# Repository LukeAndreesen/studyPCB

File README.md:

This project is a study timer that is meant to enforce productivity; an onboard
IR sensor, as well as a daughter-board hall-effect sensor module detect
a user's presence and ensure their phone is sitting on the desk and not in 
their hands. 3 daisy-chaineed shift registers control the 7-segment displays, 
and a magnetic buzzer and onboard LED's provide feedback and alerts. The 
devce connects to the user's computer via USB for power and serial connectivity
with the UI which can be interacted with using the board's buttons and 
potentiometer dial. This was my first independent PCB board, and I really
enjoyed the process of designing, soldering, and programming it!

A Bill of Materials is available as CSV in this repo, along with KiCad schematics.

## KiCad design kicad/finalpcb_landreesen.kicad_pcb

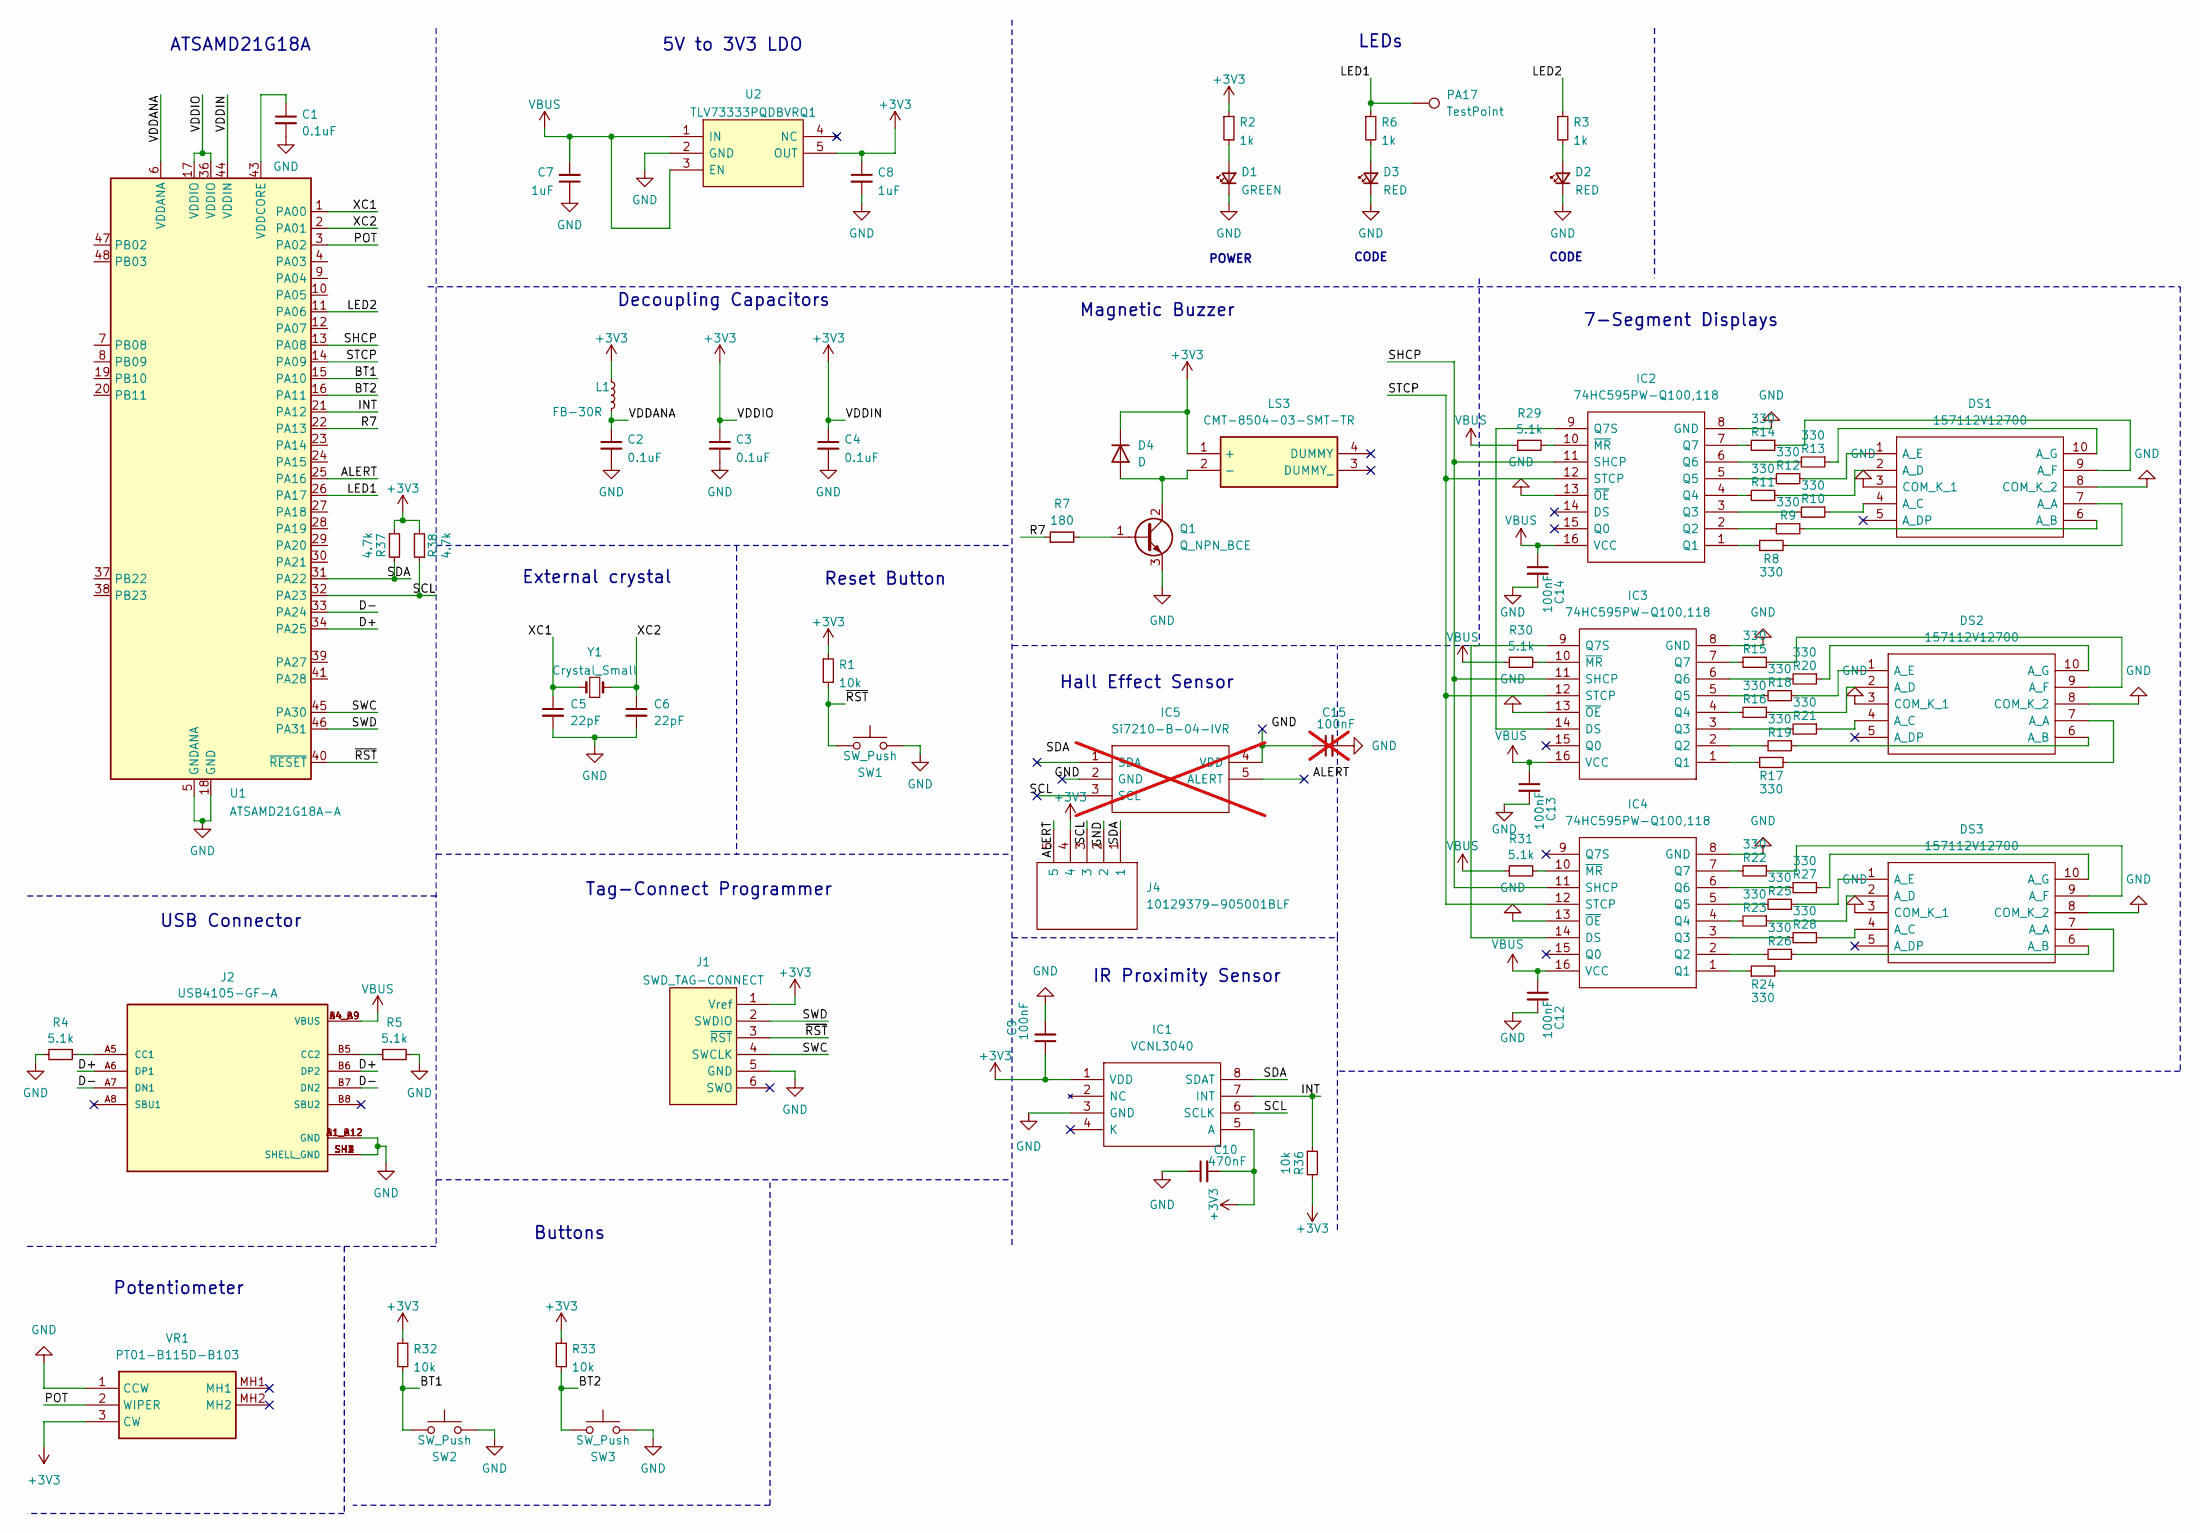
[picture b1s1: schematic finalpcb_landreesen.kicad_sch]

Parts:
C1, C2, C3, C4: 0.1uF; C_0603_1608Metric_Pad1.08x0.95mm_HandSolder
C5, C6: 22pF; C_0603_1608Metric_Pad1.08x0.95mm_HandSolder; Mouser Part Number 581-06035C220JAT2A
C7, C8: 1uF; C_0603_1608Metric_Pad1.08x0.95mm_HandSolder
C9, C12, C13, C14: 100nF; C_0603_1608Metric_Pad1.08x0.95mm_HandSolder
C10: 470nF; C_0603_1608Metric_Pad1.08x0.95mm_HandSolder
C15: 100nF; C_0603_1608Metric_Pad1.08x0.95mm_HandSolder; not fitted
D1: GREEN; LED_0603_1608Metric_Pad1.05x0.95mm_HandSolder
D2, D3: RED; LED_0603_1608Metric_Pad1.05x0.95mm_HandSolder; Mouser Part Number 710-150060RS55040
D4: D; SOD2713X115N
DS1, DS2, DS3: 157112V12700; Mouser Part Number 710-157112V12700
IC1: VCNL3040; SON108P200X400X115-8N; Mouser Part Number 78-VCNL3040
IC2, IC3, IC4: 74HC595PW-Q100,118; SOP65P640X110-16N; Mouser Part Number 771-74HC595PW-Q100
IC5: Si7210-B-04-IVR; SOT95P275X125-5N; Mouser Part Number 634-SI7210-B-04-IVR; not fitted
J1: SWD_TAG-CONNECT; Tag-Connect_TC2030-IDC-FP_2x03_P1.27mm_Vertical
J2: USB4105-GF-A; GCT_USB4105-GF-A
J4: 10129379-905001BLF; HDRRA5W67P0X254_1X5_1270X254X241P; Manufacturer_Part_Number 10129379-905001BLF
L1: FB-30R; L_0603_1608Metric_Pad1.05x0.95mm_HandSolder
LS3: CMT-8504-03-SMT-TR; CMT850403SMTTR; Mouser Part Number 179-CMT-8504-03SMTTR
PA17: TestPoint; TestPoint_Pad_D1.5mm
Q1: Q_NPN_BCE; 2SA1588GRLF
R1, R32, R33, R36: 10k; R_0603_1608Metric_Pad0.98x0.95mm_HandSolder
R2, R3, R6: 1k; R_0603_1608Metric_Pad0.98x0.95mm_HandSolder
R4, R5, R29, R30, R31: 5.1k; R_0603_1608Metric_Pad0.98x0.95mm_HandSolder
R7: 180; R_0603_1608Metric_Pad0.98x0.95mm_HandSolder
R8, R9, R10, R11, R12, R13, R14, R15, R16, R17, R18, R19, R20, R21, R22, R23, R24, R25, R26, R27, R28: 330; R_0603_1608Metric_Pad0.98x0.95mm_HandSolder
R37, R38: 4.7k; R_0603_1608Metric_Pad0.98x0.95mm_HandSolder
SW1, SW2, SW3: SW_Push; SW_SPST_TL3305A
U1: ATSAMD21G18A-A; TQFP-48_7x7mm_P0.5mm
U2: TLV73333PQDBVRQ1; SOT95P280X145-5N; Mouser Part Number 595-TLV73333PQDBVRQ1
VR1: PT01-B115D-B103; PT01B115DB103; Mouser Part Number 179-PT01-B115D-B103
Y1: Crystal_Small; Crystal_SMD_3215-2Pin_3.2x1.5mm; Mouser Part Number 815-ABS07-32.768KHZT

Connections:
+3V3: C3.1, C4.1, C8.1, C9.1, C10.2, D4.1 (K), IC1.1 (VDD), IC1.5 (A), J1.1 (Vref), J4.4, L1.1, LS3.1 (+), R1.1, R2.1, R32.1, R33.1, R36.2, R37.1, R38.2, U1.17 (VDDIO), U1.36 (VDDIO), U1.44 (VDDIN), U2.5 (OUT), VR1.3 (CW)
/ALERT: J4.5, U1.25 (PA16)
/BT1: R32.2, SW2.1, U1.15 (PA10)
/BT2: R33.2, SW3.1, U1.16 (PA11)
/D+: J2.A6 (DP1), J2.B6 (DP2), U1.34 (PA25)
/D-: J2.A7 (DN1), J2.B7 (DN2), U1.33 (PA24)
/INT: IC1.7 (INT), R36.1, U1.21 (PA12)
/LED1: PA17.1, R6.1, U1.26 (PA17)
/LED2: R3.1, U1.11 (PA06)
/POT: U1.3 (PA02), VR1.2 (WIPER)
/R7: R7.1, U1.22 (PA13)
/SCL: IC1.6 (SCLK), J4.3, R38.1, U1.32 (PA23)
/SDA: IC1.8 (SDAT), J4.1, R37.2, U1.31 (PA22)
/SHCP: IC2.11 (SHCP), IC3.11 (SHCP), IC4.11 (SHCP), U1.13 (PA08)
/STCP: IC2.12 (STCP), IC3.12 (STCP), IC4.12 (STCP), U1.14 (PA09)
/SWC: J1.4 (SWCLK), U1.45 (PA30)
/SWD: J1.2 (SWDIO), U1.46 (PA31)
/VDDANA: C2.1, L1.2, U1.6 (VDDANA)
/XC1: C5.1, U1.1 (PA00), Y1.2
/XC2: C6.1, U1.2 (PA01), Y1.1
/~RST: J1.3 (~RST), R1.2, SW1.1, U1.40 (~RESET)
GND: C1.2, C2.2, C3.2, C4.2, C5.2, C6.2, C7.1, C8.2, C9.2, C10.1, C12.2, C13.2, C14.2, C15.2, D1.1 (K), D2.1 (K), D3.1 (K), DS1.3 (COM_K_1), DS1.8 (COM_K_2), DS2.3 (COM_K_1), DS2.8 (COM_K_2), DS3.3 (COM_K_1), DS3.8 (COM_K_2), IC1.3 (GND), IC2.8 (GND), IC2.13 (~OE), IC3.8 (GND), IC3.13 (~OE), IC4.8 (GND), IC4.13 (~OE), J1.5 (GND), J2.A1_B12 (GND), J2.B1_A12 (GND), J2.SH1 (SHELL_GND), J2.SH2 (SHELL_GND), J2.SH3 (SHELL_GND), J2.SH4 (SHELL_GND), J4.2, Q1.3 (E), R4.2, R5.2, SW1.2, SW2.2, SW3.2, U1.5 (GNDANA), U1.18 (GND), U1.35 (GND), U1.42 (GND), U2.2 (GND), VR1.1 (CCW)
unnamed: C15.1, IC5.4 (VDD)
unnamed: D1.2 (A), R2.2
unnamed: D2.2 (A), R3.2
unnamed: D3.2 (A), R6.2
unnamed: D4.2 (A), LS3.2 (-), Q1.2 (C)
unnamed: DS1.7 (A_A), R8.2
unnamed: DS1.6 (A_B), R9.1
unnamed: DS1.4 (A_C), R10.1
unnamed: DS1.2 (A_D), R11.1
unnamed: DS1.1 (A_E), R12.1
unnamed: DS1.9 (A_F), R14.1
unnamed: DS1.10 (A_G), R13.1
unnamed: DS2.7 (A_A), R17.2
unnamed: DS2.6 (A_B), R19.1
unnamed: DS2.4 (A_C), R21.1
unnamed: DS2.2 (A_D), R16.1
unnamed: DS2.1 (A_E), R18.1
unnamed: DS2.9 (A_F), R15.1
unnamed: DS2.10 (A_G), R20.1
unnamed: DS3.7 (A_A), R24.2
unnamed: DS3.6 (A_B), R26.1
unnamed: DS3.4 (A_C), R28.1
unnamed: DS3.2 (A_D), R23.1
unnamed: DS3.1 (A_E), R25.1
unnamed: DS3.9 (A_F), R22.1
unnamed: DS3.10 (A_G), R27.1
unnamed: IC2.1 (Q1), R8.1
unnamed: IC2.2 (Q2), R9.2
unnamed: IC2.3 (Q3), R10.2
unnamed: IC2.4 (Q4), R11.2
unnamed: IC2.5 (Q5), R12.2
unnamed: IC2.6 (Q6), R13.2
unnamed: IC2.7 (Q7), R14.2
unnamed: IC2.9 (Q7S), IC3.14 (DS)
unnamed: IC2.10 (~MR), R29.2
unnamed: IC3.1 (Q1), R17.1
unnamed: IC3.2 (Q2), R19.2
unnamed: IC3.3 (Q3), R21.2
unnamed: IC3.4 (Q4), R16.2
unnamed: IC3.5 (Q5), R18.2
unnamed: IC3.6 (Q6), R20.2
unnamed: IC3.7 (Q7), R15.2
unnamed: IC3.9 (Q7S), IC4.14 (DS)
unnamed: IC3.10 (~MR), R30.2
unnamed: IC4.1 (Q1), R24.1
unnamed: IC4.2 (Q2), R26.2
unnamed: IC4.3 (Q3), R28.2
unnamed: IC4.4 (Q4), R23.2
unnamed: IC4.5 (Q5), R25.2
unnamed: IC4.6 (Q6), R27.2
unnamed: IC4.7 (Q7), R22.2
unnamed: IC4.10 (~MR), R31.2
unnamed: J2.A5 (CC1), R4.1
unnamed: J2.B5 (CC2), R5.1
unnamed: Q1.1 (B), R7.2
unnamed: C1.1, U1.43 (VDDCORE)
VBUS: C7.2, C12.1, C13.1, C14.1, IC2.16 (VCC), IC3.16 (VCC), IC4.16 (VCC), J2.A4_B9 (VBUS), J2.B4_A9 (VBUS), R29.1, R30.1, R31.1, U2.1 (IN), U2.3 (EN)

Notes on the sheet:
Buttons
5V to 3V3 LDO
External crystal
Tag-Connect Programmer
Decoupling Capacitors
Magnetic Buzzer
CODE
7-Segment Displays
LEDs
IR Proximity Sensor
POWER
Hall Effect Sensor
USB Connector
Potentiometer
ATSAMD21G18A
Reset Button

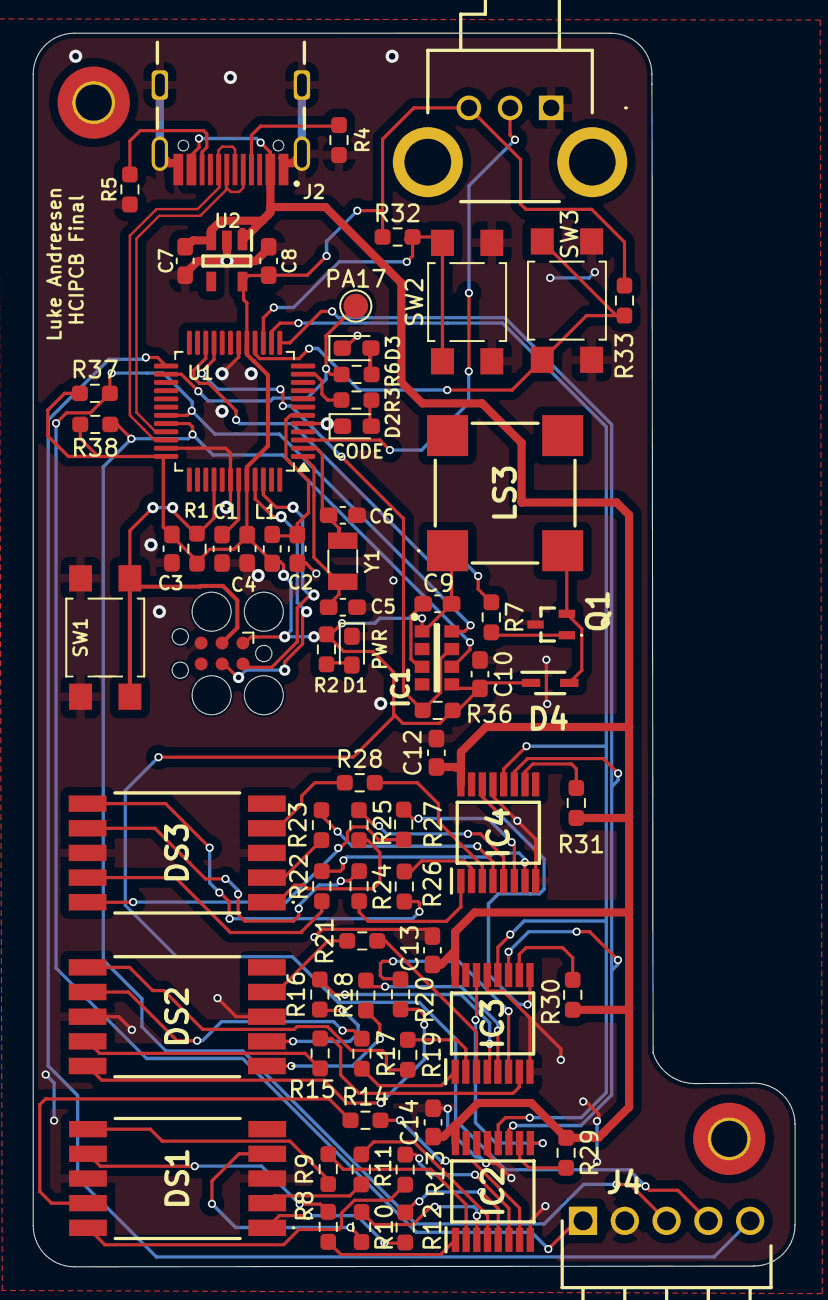
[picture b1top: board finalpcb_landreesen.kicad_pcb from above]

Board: 2 copper layers, 46.3 x 75.0 mm, 74 parts (0 on the bottom side), 78 nets.

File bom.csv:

"Reference","Value","Datasheet","Footprint","Qty","DNP"
"C1,C2,C3,C4","0.1uF","~","Capacitor_SMD:C_0603_1608Metric_Pad1.08x0.95mm_HandSolder","4",""
"C5,C6","22pF","~","Capacitor_SMD:C_0603_1608Metric_Pad1.08x0.95mm_HandSolder","2",""
"C7,C8","1uF","~","Capacitor_SMD:C_0603_1608Metric_Pad1.08x0.95mm_HandSolder","2",""
"C9,C12,C13,C14","100nF","~","Capacitor_SMD:C_0603_1608Metric_Pad1.08x0.95mm_HandSolder","4",""
"C10","470nF","~","Capacitor_SMD:C_0603_1608Metric_Pad1.08x0.95mm_HandSolder","1",""
"C15","100nF","~","Capacitor_SMD:C_0603_1608Metric_Pad1.08x0.95mm_HandSolder","1","DNP"
"D1","GREEN","~","LED_SMD:LED_0603_1608Metric_Pad1.05x0.95mm_HandSolder","1",""
"D2,D3","RED","~","LED_SMD:LED_0603_1608Metric_Pad1.05x0.95mm_HandSolder","2",""
"D4","D","https://www.vishay.com/docs/85751/1n4148ws.pdf","finalpcb:SOD2713X115N","1",""
"DS1,DS2,DS3","157112V12700","https://componentsearchengine.com/Datasheets/2/157112V12700.pdf","finalpcb:157112V12700","3",""
"IC1","VCNL3040","https://www.vishay.com/docs/84917/vcnl3040.pdf","finalpcb:SON108P200X400X115-8N","1",""
"IC2,IC3,IC4","74HC595PW-Q100,118","https://assets.nexperia.com/documents/data-sheet/74HC_HCT595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","finalpcb:SOP65P640X110-16N","3",""
"IC5","Si7210-B-04-IVR","https://componentsearchengine.com/Datasheets/2/SI7210-B-04-IVR.pdf","finalpcb:SOT95P275X125-5N","1","DNP"
"J1","SWD_TAG-CONNECT","https://www.tag-connect.com/wp-content/uploads/bsk-pdf-manag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","Connector:Tag-Connect_TC2030-IDC-FP_2x03_P1.27mm_Vertical","1",""
"J2","USB4105-GF-A","https://www.mouser.com/datasheet/2/837/Global_Connector_Tech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","hcipcb:GCT_USB4105-GF-A","1",""
"J4","10129379-905001BLF","https://cdn.amphenol-cs.com/media/wysiwyg/files/drawing/1012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","HDRRA5W67P0X254_1X5_1270X254X241P","1",""
"L1","FB-30R","https://www.mouser.com/ProductDetail/Laird-Performance-Mater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","Inductor_SMD:L_0603_1608Metric_Pad1.05x0.95mm_HandSolder","1",""
"LS3","CMT-8504-03-SMT-TR","https://www.sameskydevices.com/product/resource/cmt-8504-03-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","CMT850403SMTTR","1",""
"PA17","TestPoint","~","TestPoint:TestPoint_Pad_D1.5mm","1",""
"Q1","Q_NPN_BCE","https://www.mouser.com/datasheet/2/408/2SA1588_datasheet_en_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","finalpcb:2SA1588GRLF","1",""
"R1,R32,R33,R36","10k","~","Resistor_SMD:R_0603_1608Metric_Pad0.98x0.95mm_HandSolder","4",""
"R2,R3,R6","1k","~","Resistor_SMD:R_0603_1608Metric_Pad0.98x0.95mm_HandSolder","3",""
"R4,R5,R29,R30,R31","5.1k","~","Resistor_SMD:R_0603_1608Metric_Pad0.98x0.95mm_HandSolder","5",""
"R7","180","~","Resistor_SMD:R_0603_1608Metric_Pad0.98x0.95mm_HandSolder","1",""
"R8,R9,R10,R11,R12,R13,R14,R15,R16,R17,R18,R19,R20,R21,R22,R23,R24,R25,R26,R27,R28","330","~","Resistor_SMD:R_0603_1608Metric_Pad0.98x0.95mm_HandSolder","21",""
"R37,R38","4.7k","~","Resistor_SMD:R_0603_1608Metric_Pad0.98x0.95mm_HandSolder","2",""
"SW1,SW2,SW3","SW_Push","~","Button_Switch_SMD:SW_SPST_TL3305A","3",""
"U1","ATSAMD21G18A-A","http://ww1.microchip.com/downloads/en/DeviceDoc/SAM_D21_DA1_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","Package_QFP:TQFP-48_7x7mm_P0.5mm","1",""
"U2","TLV73333PQDBVRQ1","http://www.ti.com/lit/gpn/TLV733P-Q1","hcipcb:SOT95P280X145-5N","1",""
"VR1","PT01-B115D-B103","https://www.sameskydevices.com/product/resource/supplyframep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","finalpcb:PT01B115DB103","1",""
"Y1","Crystal_Small","~","Crystal:Crystal_SMD_3215-2Pin_3.2x1.5mm","1",""

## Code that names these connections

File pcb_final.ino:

#include <Wire.h>
#include "VCNL3040.h"
#include "si7210.h"  
/*
SOURCES:
  [1] https://www.youtube.com/watch?v=QI1IJLB42G8 - used for all shift register logic!
  [2] https://chatgpt.com/share/68372485-d47c-8005-8657-77b860ad0506 - used chatgpt to help me learn about receiving/parsing serialusb 
  [3] https://github.com/FARLY7/si7210-driver - si7210 driver library
*/

VCNL3040 proximitySensor;

// timer tracking ()
bool TIMER_STARTED = false;


// SI7210 device structure
si7210_dev_t hallSensor;
bool si7210_working = false;  // Track if SI7210 is working

const int histSize = 10;
const float MAG_THRESH = 0.40;
const int PROX_THRESH = 3; // 7 of the last 10 readings should be nonzero
const int POT = A0;
const int CODE_LED = 40;
const int HALL_LED = 41;  // Add a second LED for hall sensor indication
const int BUZZER = 38;
const int DS = 6;
const int SHCP = 4;
const int STCP = 3;
const int BT1 = 1;
const int BT2 = 0;

uint16_t prevProx[histSize] = {0};
int proxIdx = 0;
bool userPresent = true;
bool phoneDetected = true;

// Source: [1]
// decimal representation of 7 segment display values
int digits[10] = {126, 48, 109, 121, 51, 91, 95, 112, 127, 123}; // ideally used for display ... didn't work :(

void displayTest(){
  // SOURCE: [1]
  // Ideally ths would iterate through all numbers on each screen ... but doesn't work
  for (int k = 0; k < 10; k++) {       // Left digit
    for (int j = 0; j < 10; j++) {     // middle digit
      for (int i = 0; i < 10; i++) {   // Right digit
        digitalWrite(STCP, LOW);
        shiftOut(DS, SHCP, LSBFIRST, digits[i]);  // Right
        shiftOut(DS, SHCP, LSBFIRST, digits[j]);  // Middle
        shiftOut(DS, SHCP, LSBFIRST, digits[k]);  // Lef
        digitalWrite(STCP, HIGH);
        delay(200);
      }
    }
  }
}

int getPotVal(int pot_reading) {
  // read potentiometer
  float range_val = 1023.0 / 10; // potentonmeter goes up to 1023, want one of 10 values
  int val = pot_reading / 102.4;  
  if (val > 9){
    val = 9; // just in case it somehow exceeds 9
  }
  return val;
}

void checkSerialCommands() {
  // Listens for serial commands from our application to start/stop timer
  // Source: [2]
  if (SerialUSB.available()) {
    String cmd = SerialUSB.readStringUntil('\n');
    cmd.trim();

    if (cmd == "TIMER_START") {
      SerialUSB.println("Timer started!");
      // Single beep - timer started
      tone(BUZZER, 2000);   
      delay(200);
      noTone(BUZZER);
      TIMER_STARTED = true;    
    } 
    else if (cmd == "TIMER_END") {
      // Double beep - timer done
      SerialUSB.println("Timer ended!");
      TIMER_STARTED = false; 
      tone(BUZZER, 1500);   
      delay(400);
      noTone(BUZZER); 
      delay(300);
      tone(BUZZER, 1500);   
      delay(400);
      noTone(BUZZER); 
    }
  }
}


// I2C communication functions for SI7210
si7210_status_t i2c_read(uint8_t dev_id, uint8_t reg_addr, uint8_t *data, uint16_t len) {
  // Source: [3] - taken straight from examples
  Wire.beginTransmission(dev_id >> 1);  // converts to copmatible adress form (7-bit)
  Wire.write(reg_addr);
  if (Wire.endTransmission() != 0) {
    return SI7210_E_IO;
  }
  
  Wire.requestFrom((uint8_t)(dev_id >> 1), len);
  for (uint16_t i = 0; i < len; i++) {
    if (Wire.available()) {
      data[i] = Wire.read();
    } else {
      return SI7210_E_IO;
    }
  }
  return SI7210_OK;
}

si7210_status_t i2c_write(uint8_t dev_id, uint8_t reg_addr, uint8_t *data, uint16_t len) {
  // Source: [3] - taken straight from examples
  Wire.beginTransmission(dev_id >> 1);  // converts to copmatible adress form (7-bit)
  Wire.write(reg_addr);
  for (uint16_t i = 0; i < len; i++) {
    Wire.write(data[i]);
  }
  if (Wire.endTransmission() != 0) {
    return SI7210_E_IO;
  }
  return SI7210_OK;
}

void delay_ms(uint32_t period) {
  // Used for si7210 setup (via examples [3])
  delay(period);
}

void setup_proximity()
{
  // Initialize VCNL3040 proximity sensor 
  if (!proximitySensor.begin()) {
    SerialUSB.println("VCNL3040 not found");
    while (1);
  }
  SerialUSB.println("VCNL3040 initialized.");
  proximitySensor.startReading(); // now let's start reading proximty data
}

void setup_hall()
{
  // Initialize SI7210 hall effect sensor - via [3]
  hallSensor.dev_id = 0x33 << 1;  // Convert to 8-bit address for library
  // reference functions setup as per [3]
  hallSensor.read = i2c_read;
  hallSensor.write = i2c_write;
  hallSensor.delay_ms = delay_ms;
  hallSensor.threshold_callback = NULL; // not needed
  
  // Set sensor settings - as per [3]
  hallSensor.settings.range = SI7210_200mT;  // 200mT range
  hallSensor.settings.compensation = SI7210_COMPENSATION_NONE;
  hallSensor.settings.output_pin = SI7210_OUTPUT_PIN_LOW;

  // Initialize the SI7210 sensor [3]
  SerialUSB.println("Initializing SI7210 hall effect sensor");
  si7210_status_t result = si7210_init(&hallSensor);
  SerialUSB.print("Initialization result: ");
  SerialUSB.println(result);
    
  // build in redundancy - if it's not working, or detached, we should continue
  if (result != SI7210_OK) {
    SerialUSB.print("SI7210 initialization failed. Error code:");
    SerialUSB.println(result);
    SerialUSB.println("We will proceed without the hall effect sensor");
    si7210_working = false;
  } 
  else {
    SerialUSB.println("SI7210 initialized successfully!");
    si7210_working = true;
  }
}

void setup() {
  // LED's for debuggin
  pinMode(CODE_LED, OUTPUT);
  pinMode(HALL_LED, OUTPUT); 
  // pins for shift registers for display
  pinMode(DS, OUTPUT);
  pinMode(SHCP, OUTPUT);
  pinMode(STCP, OUTPUT);
  // button pins .. didn't end up using though
  pinMode(BT1, INPUT);
  pinMode(BT2, INPUT);
  
  SerialUSB.begin(9600);
  while (!SerialUSB); // let serial usb setup first

  // Initialize I2C
  Wire.begin();

  // setup sensors
  setup_proximity();
  setup_hall();

  SerialUSB.println("Setup complete. Starting main loop...");
  delay(5000); // a delay to get set up
}

void loop() {
  checkSerialCommands(); // check for timer start/stop via web app
  // Read proximity sensor
  uint16_t proximity = proximitySensor.readPSData();
  
  // Read potentiometer
  int pot_reading = analogRead(POT);
  int pot_val = getPotVal(pot_reading);
  SerialUSB.print("Dial Value: ");
  SerialUSB.print(pot_val);
  SerialUSB.print(" | ");


  
  // Only try to read hall sensor if it's working - suggested in [3]
  float magneticField = 0.0;
  si7210_status_t result = SI7210_E_DEV_NOT_FOUND;
  
  // result will be SI7210_OK if reading works and saved to magneticField, else something went wrong
  if (si7210_working) {
    result = si7210_get_field_strength(&hallSensor, &magneticField);
  }
  
  if (result != SI7210_OK) {
    SerialUSB.println("N/A (SI7210 not available)");
  
  }
  // any singnificant change in magnetic field (+ or -) should be detected (phone is next to sensor)
  if (abs(magneticField) < MAG_THRESH)
  {
    SerialUSB.print("Phone: False |");
    phoneDetected = false;
  }
  else
  {
     SerialUSB.print("Phone: True | ");
     phoneDetected = true;
  }

  // If we have started timer and we move away from desk or move phone ...  BUZZ!
  if (TIMER_STARTED)
  {
    (phoneDetected & (proximity >= 5)) ? noTone(BUZZER) : tone(BUZZER, 4000);
  }
  
  // unused logic -- ideally we'd make the proxmity software a bit more robust to account for sensor sensitivity
  prevProx[proxIdx] = proximity;
  proxIdx = (proxIdx + 1) % 10; // we want to look at previous 10 readings

  // Count how many of the last 10 readings are zero
  int num_zeros = 0;
  for (int i = 0; i < histSize; i++) {
    if ((prevProx[i] == 0) or (prevProx[i] == 1))  {
      num_zeros++;
    }
  }

  // we have moved away from desk 
  if (proximity < 5){
    userPresent = false;
    SerialUSB.println(" At desk: False");
  }
  else
  {
    userPresent = true;
    SerialUSB.println(" At desk: True");
  }


  delay(100); // give a slight timing gap
}

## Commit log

2025-05-29 bill of materials
2025-05-29 readme
2025-05-29 readme update
2025-05-29 kicad
